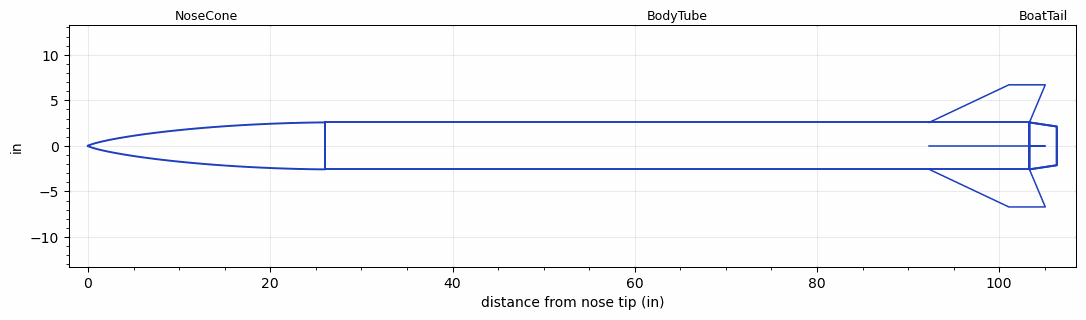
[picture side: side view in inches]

<RASAeroDocument>
 <FileVersion>2</FileVersion>
 <RocketDesign>
  <NoseCone>
   <Length>26</Length>
   <Diameter>5.15</Diameter>
   <Shape>LV-Haack</Shape>
   <Location>0</Location>
  </NoseCone>
  <BodyTube>
   <Length>77.315</Length>
   <Diameter>5.15</Diameter>
   <Location>26</Location>
   <BoattailLength>3</BoattailLength>
   <BoattailRearDiameter>4.25</BoattailRearDiameter>
   <Fin>
    <Count>4</Count>
    <Chord>11</Chord>
    <Span>4.125</Span>
    <SweepDistance>8.736</SweepDistance>
    <TipChord>4</TipChord>
    <Thickness>0.187</Thickness>
    <Location>11</Location>
    <AirfoilSection>Square</AirfoilSection>
   </Fin>
  </BodyTube>
  <BoatTail>
   <Length>3</Length>
   <Diameter>5.15</Diameter>
   <RearDiameter>4.25</RearDiameter>
   <Location>103.315</Location>
  </BoatTail>
  <Surface>Smooth Paint</Surface>
  <ModifiedBarrowman>False</ModifiedBarrowman>
  <Turbulence>False</Turbulence>
  <UseBooster1>False</UseBooster1>
  <UseBooster2>False</UseBooster2>
 </RocketDesign>
 <LaunchSite>
  <Altitude>0</Altitude>
  <Pressure>0</Pressure>
  <RodAngle>0</RodAngle>
  <RodLength>4</RodLength>
  <Temperature>74</Temperature>
  <WindSpeed>0</WindSpeed>
 </LaunchSite>
 <Recovery>
  <Altitude1>1000</Altitude1>
  <Altitude2>1000</Altitude2>
  <DeviceType1>None</DeviceType1>
  <DeviceType2>None</DeviceType2>
  <Event1>False</Event1>
  <Event2>False</Event2>
  <Size1>1</Size1>
  <Size2>1</Size2>
  <EventType1>None</EventType1>
  <EventType2>None</EventType2>
  <CD1>1.33</CD1>
  <CD2>1.33</CD2>
 </Recovery>
 <SimulationList>
  <Simulation>
   <SustainerEngine>M2500T  (AT)</SustainerEngine>
   <SustainerLaunchWt>0</SustainerLaunchWt>
   <SustainerCG>0</SustainerCG>
   <SustainerIgnitionDelay>0</SustainerIgnitionDelay>
   <Booster1SeparationDelay>0</Booster1SeparationDelay>
   <Booster1IgnitionDelay>0</Booster1IgnitionDelay>
   <IncludeBooster1>False</IncludeBooster1>
   <Booster2Delay>0</Booster2Delay>
   <IncludeBooster2>False</IncludeBooster2>
  </Simulation>
 </SimulationList>
</RASAeroDocument>
